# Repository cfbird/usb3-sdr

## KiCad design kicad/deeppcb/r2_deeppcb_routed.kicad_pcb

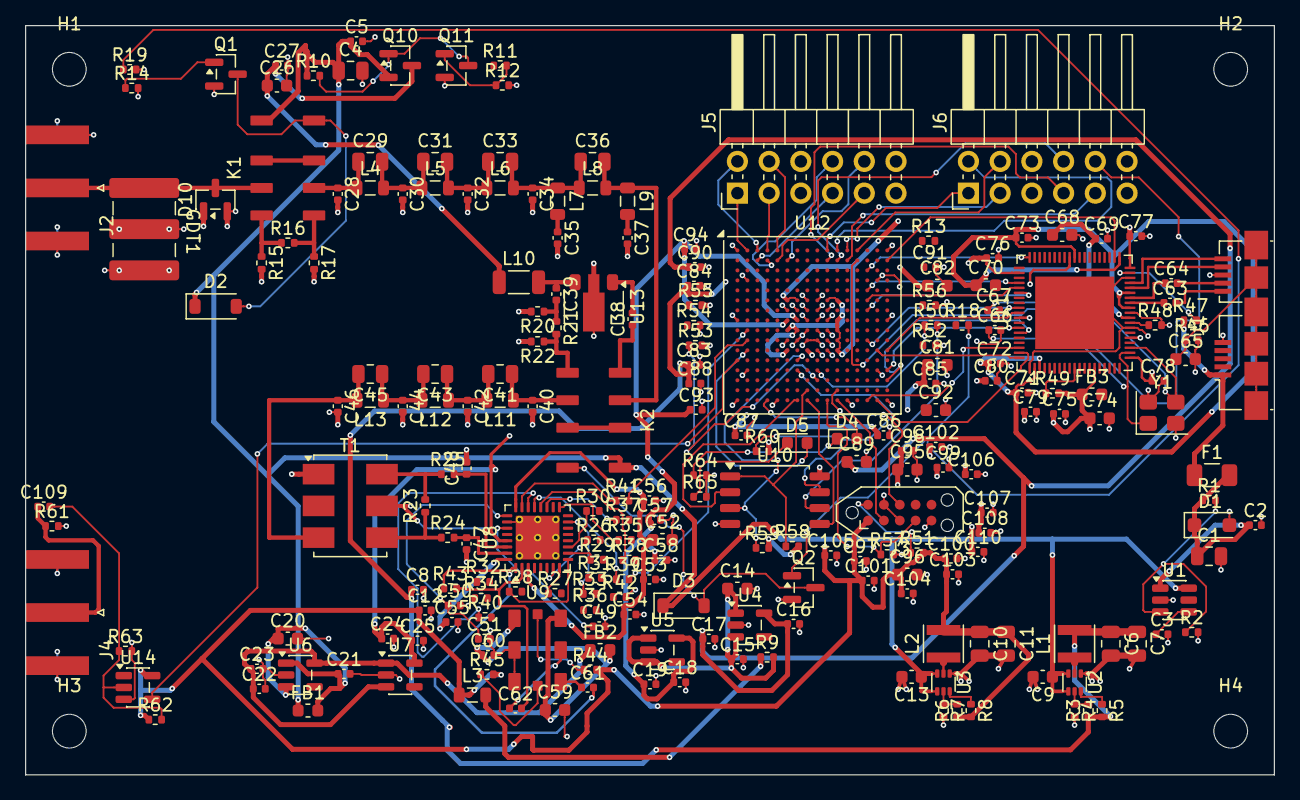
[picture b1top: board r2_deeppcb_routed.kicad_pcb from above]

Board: 4 copper layers, 100.0 x 60.0 mm, 231 parts (0 on the bottom side), 203 nets.

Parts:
C1, C4, C6, C7, C10, C11: 22u; C_0805_2012Metric
C2, C5, C8, C12, C17, C19, C21, C23, C25, C27, C38, C39, C49, C51, C53, C54, C55, C56, C58, C60, C61, C62, C63, C64, C69, C71, C72, C73, C75, C76, C77, C78, C79, C80, C83, C84, C85, C86, C87, C88, C90, C91, C93, C94, C97, C98, C99, C100, C101, C102, C103, C104, C105, C106, C107, C108, C109, C110: 100n; C_0402_1005Metric
C3: 1n; C_0402_1005Metric
C9, C13, C14, C20, C26, C52, C59, C74, C81, C82, C89, C92, C95, C96: 10u; C_0603_1608Metric
C15, C16, C18, C22, C24, C50, C57: 1u; C_0402_1005Metric
C28, C40: 62p C0G 2%; C_0402_1005Metric
C29, C41: 62p C0G 2%; C_0805_2012Metric
C30, C42: 130p C0G 2%; C_0402_1005Metric
C31, C43: 30p C0G 2%; C_0805_2012Metric
C32, C44: 160p C0G 2%; C_0402_1005Metric
C33, C45: 11p C0G 2%; C_0805_2012Metric
C34, C46: 91p C0G 2%; C_0402_1005Metric
C35: 39p C0G 2%; C_0402_1005Metric
C36: 15p C0G 2%; C_0805_2012Metric
C37: 47p C0G 2%; C_0402_1005Metric
C47, C48: 10p C0G; C_0402_1005Metric
C65: 4.7n 250V; C_0603_1608Metric
C66, C67: 33p C0G; C_0402_1005Metric
C68, C70: 4.7u; C_0603_1608Metric
D1: SMF5.0A; D_SOD-123F
D2, D3: 1N4148W; D_SOD-123
D4, D5: LED green; LED_0603_1608Metric
D10: BAV99; SOT-23
F1: 1.1A; Fuse_1206_3216Metric
FB1, FB2, FB3: 600R@100MHz; L_0603_1608Metric
GDT1: 2038-09-SM (90V); GDT_Bourns_2038
H1, H2, H3, H4: MountingHole_2.7mm_M2.5
J1: USB3 Micro-B; USB3_Micro-B_Connfly_DS1104-01
J2: SMA RF IN; SMA_Amphenol_132289_EdgeMount
J3: TC2050 JTAG; Tag-Connect_TC2050-IDC-NL_2x05_P1.27mm_Vertical
J4: SMA 10MHz REF; SMA_Amphenol_132289_EdgeMount
J5: PMOD0; PinHeader_2x06_P2.54mm_Horizontal
J6: PMOD1; PinHeader_2x06_P2.54mm_Horizontal
K1, K2: HFD4/5-SR; Relay_DPDT_Hongfa_HFD4-SR
L1, L2: 1u 2A shielded; L_Taiyo-Yuden_NR-30xx
L3: 1u; L_0805_2012Metric
L4, L8, L11: 180n 0805HP 2%; L_0805_2012Metric
L5, L6, L12, L13: 270n 0805HP 2%; L_0805_2012Metric
L7: 82n 0805HP 2%; L_0805_2012Metric
L9: 47n 0805HP 2%; L_0805_2012Metric
L10: 15u bias choke; L_1206_3216Metric
Q1, Q2, Q11: 2N7002; SOT-23
Q10: AO3401A; SOT-23
R1, R2, R5, R8, R10, R12, R14, R19: 100k; R_0402_1005Metric
R3: 100k 1%; R_0402_1005Metric
R4: 120k 1%; R_0402_1005Metric
R6: 226k 1%; R_0402_1005Metric
R7: 49.9k 1%; R_0402_1005Metric
R9: 0.47; R_0402_1005Metric
R11, R13, R18, R43: 100; R_0402_1005Metric
R15, R17: 61.9 1%; R_0402_1005Metric
R16: 249 1%; R_0402_1005Metric
R20, R22: 294 1%; R_0402_1005Metric
R21: 17.8 1%; R_0402_1005Metric
R23: 200 1%; R_0402_1005Metric
R24, R25: 33; R_0402_1005Metric
R26, R27, R28, R29, R30, R31, R32, R33, R34, R35, R36, R37, R38, R39, R40, R41: 22; R_0402_1005Metric
R42: 10k 1%; R_0402_1005Metric
R44, R45, R57, R58: 4.7k; R_0402_1005Metric
R46: 1M; R_0402_1005Metric
R47, R54, R55, R56: 1k; R_0402_1005Metric
R48: 1.6k 1%; R_0402_1005Metric
R49, R51, R52, R53, R59, R60, R62, R63: 10k; R_0402_1005Metric
R50: 50 (place at FPGA); R_0402_1005Metric
R61: 49.9; R_0402_1005Metric
R64, R65: 330; R_0402_1005Metric
T1: ADT4-6T+; Mini-Circuits_CD637_H5.23mm
U1: TPS22918DBVR; SOT-23-6
U2: TPS62A02ADRLR; SOT-563
U3: TPS62A02ADRLR (forced PWM); SOT-563
U4: TLV75525PDBVR; SOT-23-5
U5, U7: TPS7A2018PDBVR; SOT-23-5
U6: TPS7A2033PDBVR; SOT-23-5
U8: AD9649BCPZ-80; LFCSP-32-1EP_5x5mm_P0.5mm_EP3.5x3.5mm_ThermalVias
U9: LMK61E2-100M00SIAR; TI_SIA0008B_QFM-8_7x5mm
U10: W25Q128JVSIQ; SOIC-8_5.3x5.3mm_P1.27mm
U11: FT601Q-B-T; QFN-76-1EP_9x9mm_P0.4mm_EP5.81x6.31mm
U12: LFE5U-25F-6BG256C; BGA-256_14.0x14.0mm_Layout16x16_P0.8mm_Ball0.45mm_Pad0.32mm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
U13: PHA-13LN+; SOT-89-3
U14: 74LVC1G17; SOT-23-5
Y1: 30MHz 20pF X322530MSB4SI; Crystal_SMD_3225-4Pin_3.2x2.5mm

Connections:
1V1: C6.1, C7.1, C8.1, C81.1, C82.1, C83.1, C84.1, C85.1, C86.1, C87.1, C88.1, L1.2, R3.1, R5.2, U12.G6, U12.G7, U12.G9, U12.L8, U12.L9, U12.L10
1V8_A: C24.1, C25.1, C52.1, C53.1, C54.1, C55.1, C56.1, U7.5, U8.3, U8.24, U8.29, U8.32
1V8_D: C18.1, C19.1, C57.1, C58.1, C92.1, C93.1, C94.1, U5.5, U8.13, U12.H6, U12.H7
2V5: C16.1, C17.1, C89.1, C90.1, C91.1, U4.5, U12.G11, U12.L7
3V3_A: C22.1, C23.1, FB2.1, U6.5, U7.1, U7.3
3V3_D: C10.1, C11.1, C12.1, C74.1, C75.1, C76.1, C77.1, C78.1, C79.1, C80.1, C95.1, C96.1, C97.1, C98.1, C99.1, C100.1, C101.1, C102.1, C103.1, C104.1, C105.1, C106.1, C107.1, C108.1, C110.1, FB3.1, J3.1, J5.6, J5.12, J6.6, J6.12, L2.2, L3.1, R6.1, R8.2, R44.2, R45.2, R49.2, R51.2, R52.2, R53.2, R55.2, R58.2, R59.2, R60.2, R62.1, U10.8, U11.14, U11.20, U11.24, U11.38, U11.49, U11.59, U11.68, U12.F6, U12.F7, U12.F10, U12.F11, U12.H11, U12.J6, U12.J7, U12.J11, U12.K11, U12.L6, U12.L11, U14.5
5V_LNA: C26.1, C27.1, L10.1, Q10.3
5V_SW: C4.1, C5.1, C9.1, C13.1, D2.1, D3.1, FB1.1, K1.1, K2.1, Q10.2, R10.1, U1.6, U2.3, U2.4, U3.3, U3.4
/ADC and clock/3V3_CLK: C59.1, C60.1, FB2.2, U9.1, U9.6
/ADC and clock/ADC_CLKN: C62.2, R43.2, U8.2
/ADC and clock/ADC_CLKP: C61.2, R43.1, U8.1
/ADC and clock/ADC_D0_R: R26.1, U8.7
/ADC and clock/ADC_D1_R: R27.1, U8.8
/ADC and clock/ADC_D2_R: R28.1, U8.9
/ADC and clock/ADC_D3_R: R29.1, U8.10
/ADC and clock/ADC_D4_R: R30.1, U8.11
/ADC and clock/ADC_D5_R: R31.1, U8.12
/ADC and clock/ADC_D6_R: R32.1, U8.14
/ADC and clock/ADC_D7_R: R33.1, U8.15
/ADC and clock/ADC_D8_R: R34.1, U8.16
/ADC and clock/ADC_D9_R: R35.1, U8.17
/ADC and clock/ADC_D10_R: R36.1, U8.18
/ADC and clock/ADC_D11_R: R37.1, U8.19
/ADC and clock/ADC_D12_R: R38.1, U8.20
/ADC and clock/ADC_D13_R: R39.1, U8.21
/ADC and clock/ADC_DCO_R: R40.1, U8.22
/ADC and clock/ADC_OR_R: R41.1, U8.23
/ADC and clock/ADC_RBIAS: R42.1, U8.28
/ADC and clock/ADC_VREF: C50.1, C51.1, U8.25
/ADC and clock/LMK_OUTN: C62.1, U9.5
/ADC and clock/LMK_OUTP: C61.1, U9.4
/FPGA/CCLK_FPGA: R50.1, U12.N9
/FPGA/D4_K: D4.1, R64.1
/FPGA/D5_K: D5.1, R65.1
/FPGA/FLASH_CS_N: R58.1, U10.1, U12.R8
/FPGA/FLASH_IO0: U10.5, U12.T8
/FPGA/FLASH_IO1: U10.2, U12.T7
/FPGA/FLASH_IO2: R59.1, U10.3, U12.M7
/FPGA/FLASH_IO3: R60.1, U10.7, U12.N7
/FPGA/FPGA_CCLK: R50.2, U10.6
/FPGA/FPGA_CFG0: R54.1, U12.N10
/FPGA/FPGA_CFG1: R55.1, U12.P10
/FPGA/FPGA_CFG2: R56.1, U12.R10
/FPGA/FPGA_DONE: R53.1, U12.P9
/FPGA/FPGA_INIT_N: R52.1, U12.T9
/FPGA/FPGA_PROGRAM_N: J3.10, R51.1, U12.R9
/FPGA/FPGA_TCK: J3.4, R57.1, U12.T10
/FPGA/FPGA_TDI: J3.8, U12.R11
/FPGA/FPGA_TDO: J3.6, U12.M10
/FPGA/FPGA_TMS: J3.2, U12.T11
/FPGA/LED0: D4.2, U12.T4
/FPGA/LED1: D5.2, U12.L2
/FPGA/PMOD0_0: J5.1, U12.A2
/FPGA/PMOD0_1: J5.2, U12.A3
/FPGA/PMOD0_2: J5.3, U12.A4
/FPGA/PMOD0_3: J5.4, U12.A5
/FPGA/PMOD0_4: J5.7, U12.B3
/FPGA/PMOD0_5: J5.8, U12.B4
/FPGA/PMOD0_6: J5.9, U12.B5
/FPGA/PMOD0_7: J5.10, U12.B6
/FPGA/PMOD1_0: J6.1, U12.A10
/FPGA/PMOD1_1: J6.2, U12.A11
/FPGA/PMOD1_2: J6.3, U12.A12
/FPGA/PMOD1_3: J6.4, U12.A13
/FPGA/PMOD1_4: J6.7, U12.B10
/FPGA/PMOD1_5: J6.8, U12.B11
/FPGA/PMOD1_6: J6.9, U12.B12
/FPGA/PMOD1_7: J6.10, U12.B13
/FPGA/REF10M: U12.M1, U14.4
/FPGA/REF_AC: C109.2, R62.2, R63.1, U14.2
/FPGA/REF_IN: C109.1, J4.1, R61.1
/Power/3V3_D_F: C14.1, C15.1, R9.2, U4.1, U4.3, U5.1, U5.3
/Power/3V3_PF: L3.2, R9.1
/Power/5V_A: C20.1, C21.1, FB1.2, U6.1, U6.3
/Power/FB_1V1: R3.2, R4.1, U2.5
/Power/FB_3V3: R6.2, R7.1, U3.5
/Power/LS_CT: C3.1, U1.4
/Power/LS_ON: R1.2, R2.1, U1.3
/Power/PG_1V1: R5.1, U2.6
/Power/PG_3V3: R8.1, U3.6
/Power/Q10_G: Q10.1, Q11.3, R10.2
/Power/Q11_G: Q11.1, R11.2, R12.1
/Power/SW_1V1: L1.1, U2.2
/Power/SW_3V3: L2.1, U3.2
/Power/VBUS_F: C1.1, C2.1, D1.1, F1.2, R1.1, U1.1
/RF front end/AIN_N_T: R23.2, R25.1, T1.6
/RF front end/AIN_P_T: R23.1, R24.1, T1.4
/RF front end/K1_COIL: D2.2, K1.8, Q1.3
/RF front end/K2_COIL: D3.2, K2.8, Q2.3
/RF front end/LNA_BYP: K2.2, K2.7
/RF front end/LNA_IN: C38.1, K2.4
/RF front end/LNA_O: C39.2, R20.1, R21.1
/RF front end/LNA_PAD_OUT: K2.5, R21.2, R22.1
/RF front end/LNA_RFIN: C38.2, U13.1
/RF front end/LNA_RFOUT: C39.1, L10.2, U13.3
/RF front end/LPF1_N2: C29.2, C30.1, C31.1, L4.2, L5.1
/RF front end/LPF1_N4: C31.2, C32.1, C33.1, L5.2, L6.1
/RF front end/LPF1_OUT: C33.2, C34.1, C36.1, L6.2, L7.1, L8.1
/RF front end/LPF2_IN: C40.1, C41.1, K2.6, L11.1
/RF front end/LPF2_N2: C41.2, C42.1, C43.1, L11.2, L12.1
/RF front end/LPF2_N4: C43.2, C44.1, C45.1, L12.2, L13.1
/RF front end/LPF2_OUT: C45.2, C46.1, L13.2, T1.3
/RF front end/NOTCH_OUT: C36.2, K2.3, L8.2, L9.1
/RF front end/PAD_BYP: K1.2, K1.7
/RF front end/PAD_IN: K1.4, R15.1, R16.1
/RF front end/PAD_OUT: K1.5, R16.2, R17.1
/RF front end/Q1_G: Q1.1, R13.2, R14.1
/RF front end/Q2_G: Q2.1, R18.2, R19.1
/RF front end/RF_A: C28.1, C29.1, K1.6, L4.1
/RF front end/RF_IN: D10.3, GDT1.1, J2.1, K1.3
/RF front end/TRAP1: C35.1, L7.2
/RF front end/TRAP3: C37.1, L9.2
/USB 3 bridge/FT_1V0: C70.1, C71.1, C72.1, C73.1, U11.2, U11.3, U11.30, U11.33, U11.39, U11.48
/USB 3 bridge/FT_RREF: R48.1, U11.27
/USB 3 bridge/FT_SIWU: R49.1, U11.10
/USB 3 bridge/FT_TXN: C63.1, U11.31
/USB 3 bridge/FT_TXP: C64.1, U11.32
/USB 3 bridge/FT_VBUS: R47.2, U11.37
/USB 3 bridge/FT_VDDA: C68.1, C69.1, FB3.2, U11.28
/USB 3 bridge/FT_XI: C66.1, U11.21, Y1.1
/USB 3 bridge/FT_XO: C67.1, U11.22, Y1.3
/USB 3 bridge/USB_D_N: J1.2, U11.25
/USB 3 bridge/USB_D_P: J1.3, U11.23
/USB 3 bridge/USB_SHIELD: C65.1, J1.11, R46.1
/USB 3 bridge/USB_SSRXN: J1.9, U11.34
/USB 3 bridge/USB_SSRXP: J1.10, U11.35
/USB 3 bridge/USB_SSTXN: C63.2, J1.6
/USB 3 bridge/USB_SSTXP: C64.2, J1.7
ADC_CSB: U8.4, U12.E3
ADC_D0: R26.2, U12.B1
ADC_D1: R27.2, U12.B2
ADC_D2: R28.2, U12.C1
ADC_D3: R29.2, U12.C2
ADC_D4: R30.2, U12.D1
ADC_D5: R31.2, U12.E2
ADC_D6: R32.2, U12.E1
ADC_D7: R33.2, U12.F2
ADC_D8: R34.2, U12.F1
ADC_D9: R35.2, U12.G2
ADC_D10: R36.2, U12.G1
ADC_D11: R37.2, U12.H2
ADC_D12: R38.2, U12.J1
ADC_D13: R39.2, U12.J2
ADC_DCO: R40.2, U12.K1
ADC_OR: R41.2, U12.K2
ADC_SCLK: U8.5, U12.C3
ADC_SDIO: U8.6, U12.D3
ADC_VCM: C49.1, T1.5, U8.27
ADC_VINN: C48.1, R25.2, U8.30
ADC_VINP: C47.1, R24.2, U8.31
FT_BE0: U11.4, U12.M15
FT_BE1: U11.5, U12.P15
FT_BE2: U11.6, U12.R12
FT_BE3: U11.7, U12.R13
FT_CLK: U11.58, U12.K16
FT_D0: U11.40, U12.B16
FT_D1: U11.41, U12.C16
FT_D2: U11.42, U12.D16
FT_D3: U11.43, U12.E16
FT_D4: U11.44, U12.F16
FT_D5: U11.45, U12.G16
FT_D6: U11.46, U12.J16
FT_D7: U11.47, U12.B15
FT_D8: U11.50, U12.C15
FT_D9: U11.51, U12.E15
FT_D10: U11.52, U12.F15
FT_D11: U11.53, U12.G15
FT_D12: U11.54, U12.H15
FT_D13: U11.55, U12.J15
FT_D14: U11.56, U12.K15
FT_D15: U11.57, U12.C14
FT_D16: U11.60, U12.D14
FT_D17: U11.61, U12.E14
FT_D18: U11.62, U12.F14
FT_D19: U11.63, U12.G14
FT_D20: U11.64, U12.H14
FT_D21: U11.65, U12.J14
FT_D22: U11.66, U12.K14
FT_D23: U11.67, U12.L16
FT_D24: U11.69, U12.M16
FT_D25: U11.70, U12.N16
FT_D26: U11.71, U12.P16
FT_D27: U11.72, U12.R16
FT_D28: U11.73, U12.T13
FT_D29: U11.74, U12.T14
FT_D30: U11.75, U12.T15
FT_D31: U11.76, U12.L15
FT_GPIO0: U11.17, U12.P13
FT_GPIO1: U11.18, U12.P14
FT_OE_N: U11.13, U12.N14
FT_RD_N: U11.12, U12.M14
FT_RESET_N: U11.15, U12.P11
FT_RXF_N: U11.9, U12.R15
FT_TXE_N: U11.8, U12.R14
FT_WAKEUP_N: U11.16, U12.P12
FT_WR_N: U11.11, U12.L14
GND: C1.2, C2.2, C3.2, C4.2, C5.2, C6.2, C7.2, C8.2, C9.2, C10.2, C11.2, C12.2, C13.2, C14.2, C15.2, C16.2, C17.2, C18.2, C19.2, C20.2, C21.2, C22.2, C23.2, C24.2, C25.2, C26.2, C27.2, C28.2, C30.2, C32.2, C34.2, C35.2, C37.2, C40.2, C42.2, C44.2, C46.2, C47.2, C48.2, C49.2, C50.2, C51.2, C52.2, C53.2, C54.2, C55.2, C56.2, C57.2, C58.2, C59.2, C60.2, C65.2, C66.2, C67.2, C68.2, C69.2, C70.2, C71.2, C72.2, C73.2, C74.2, C75.2, C76.2, C77.2, C78.2, C79.2, C80.2, C81.2, C82.2, C83.2, C84.2, C85.2, C86.2, C87.2, C88.2, C89.2, C90.2, C91.2, C92.2, C93.2, C94.2, C95.2, C96.2, C97.2, C98.2, C99.2, C100.2, C101.2, C102.2, C103.2, C104.2, C105.2, C106.2, C107.2, C108.2, C110.2, D1.2, D10.1, D10.2, GDT1.2, GDT1.3, J1.5, J1.8, J2.2, J3.3, J3.5, J3.9, J4.2, J5.5, J5.11, J6.5, J6.11, Q1.2, Q2.2, Q11.2, R2.2, R4.2, R7.2, R12.2, R14.2, R15.2, R17.2, R19.2, R20.2, R22.2, R42.2, R46.2, R48.2, R54.2, R56.2, R57.2, R61.2, R63.2, R64.2, R65.2, T1.1, U1.2, U2.1, U3.1, U4.2, U5.2, U6.2, U7.2, U8.26, U8.33, U9.2, U9.3, U10.4, U11.1, U11.26, U11.29, U11.36, U11.77, U12.A1, U12.A16, U12.D2, U12.D15, U12.F8, U12.F9, U12.G8, U12.G10, U12.H1, U12.H8, U12.H9, U12.H10, U12.H16, U12.J8, U12.J9, U12.J10, U12.K6, U12.K7, U12.K8, U12.K9, U12.K10, U12.N2, U12.N15, U12.T1, U12.T5, U12.T12, U12.T16, U13.2, U14.3, Y1.2, Y1.4
LMK_SCL: R45.1, U9.8, U12.N1
LMK_SDA: R44.1, U9.7, U12.P1
LNA_EN: R11.1, U12.T3
RLY_LNA: R18.1, U12.T2
RLY_PAD: R13.1, U12.R1
VBUS: F1.1, J1.1, R47.1
